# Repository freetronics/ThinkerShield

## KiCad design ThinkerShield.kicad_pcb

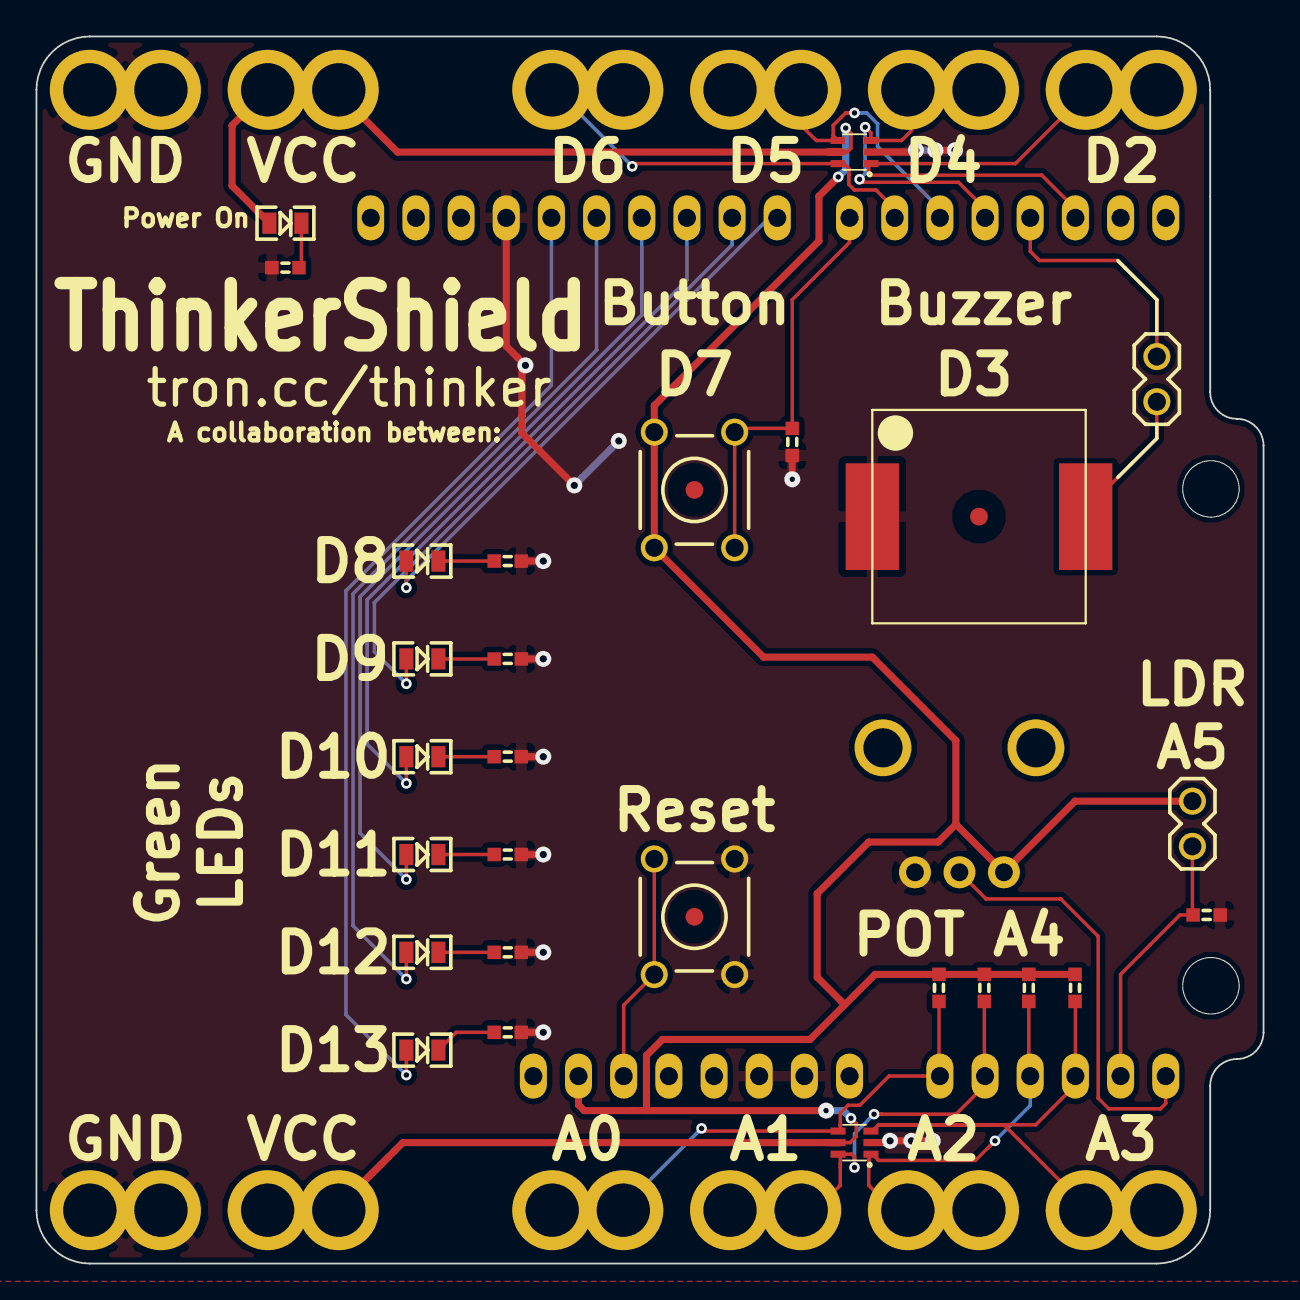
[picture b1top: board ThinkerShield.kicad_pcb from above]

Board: 2 copper layers, 69.0 x 69.0 mm, 46 parts (1 on the bottom side), 29 nets.

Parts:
FIDUCIAL: val**; FIDUCIAL
FIDUCIAL#2, FIDUCIAL#3: val**; FIDUCIAL
JP1, JP2, JP3, JP4, JP5, JP6, JP7, JP8, JP9, JP10, JP11, JP12: M01; ALLIGATOR_CLIP_CONN
JP13: JUMPER2; 1X02
LED1, LED2, LED3, LED4, LED5, LED6: GREEN; LED-0805
LED7: BLUE; LED-0805
LOGO_FREETRONICS: val**; LOGO_FREETRONICS_33mm
LOGO_FREETRONICS#2: val**; LOGO_FREETRONICS_14mm_SolderMask
PH1: LDR GL5516; 1X02
R1: 1K; 0603
R2: 10K; 0603
R3, R4, R10, R11, R12, R13: 470R; 0603
R5, R7, R8, R9: 22M; 0603
R6: 2.2K; 0603
SHIELD1: ARDUINO_SHIELD
SW1, SW2: SW_PUSHBUTTON; SW_PUSHBUTTON_PTH
TV1, TV2: SMF05C; SOT363
U1: BUZZER; BUZZER-12X12-SMT
VR1: 10K; POT_RV09_VERT

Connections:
/A0: JP1.1, R5.1, SHIELD1.AD0, TV1.4
/A1: JP2.1, R7.1, SHIELD1.AD1, TV1.6
/A2: JP3.1, R8.1, SHIELD1.AD2, TV1.1
/A3: JP4.1, R9.1, SHIELD1.AD3, TV1.3
/A4: PH1.2, R1.1, SHIELD1.AD4
/A5: SHIELD1.AD5, VR1.W
/BUZZER: JP13.2, U1.2
/D2: JP9.1, SHIELD1.2, TV2.1
/D3: JP13.1, SHIELD1.3
/D4: JP10.1, SHIELD1.4, TV2.3
/D5: JP11.1, SHIELD1.5, TV2.4
/D6: JP12.1, SHIELD1.6, TV2.6
/D7: R2.1, SHIELD1.7, SW2.2
/D8: LED1.A, SHIELD1.8
/D9: LED2.A, SHIELD1.9
/D10: LED3.A, SHIELD1.10
/D11: LED4.A, SHIELD1.11
/D12: LED5.A, SHIELD1.12
/D13: LED6.A, SHIELD1.13
GND: JP7.1, JP8.1, R1.2, R2.2, R3.1, R4.1, R6.1, R10.1, R11.1, R12.1, R13.1, SHIELD1.GND1, SHIELD1.GND2, SHIELD1.GND3, SW1.2, TV1.2, TV2.2, U1.1, VR1.1
IORef: JP5.1, JP6.1, LED7.A, PH1.1, R5.2, R7.2, R8.2, R9.2, SHIELD1.IO_R, SW2.1, TV1.5, TV2.5, VR1.2
unnamed: LED1.K, R3.2
unnamed: LED2.K, R4.2
unnamed: LED3.K, R10.2
unnamed: LED4.K, R11.2
unnamed: LED5.K, R12.2
unnamed: LED6.K, R13.2
unnamed: LED7.K, R6.2
unnamed: SHIELD1.RST, SW1.1

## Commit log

2015-05-04 First commit, first cut of design
2015-05-04 Remove WS2812B LEDs, add sixth green LED for D13
2015-05-04 Rearrange ESD protection traces, update silkscreen
2015-05-04 Add schematic PDF
2015-05-04 Update gitignore
2015-06-04 Swap TVDS to SMF05C, swap 22M resistors to individual, add body outline around RV09
2015-06-04 Swap pot orientation so CCW = min value
2015-06-04 Add power LED
2015-06-04 Grow alligator clip holes
2015-08-03 Swap A4/A5 to be compatible with older Thinkup boards
2015-08-10 Spread out LEDs, use better MAAS logo
2015-08-27 Split resistor packs into individual resistors, spread LEDs out some more
    Also includes upgrade to KiCad 2015-08 which no longer uses .cmp files
2015-08-27 Resize board designator labels

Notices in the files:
ThinkerShield.kicad_pcb:
Copyright (C) 2015 Freetronics Pty Ltd
TAPR Open Hardware License: tapr.org/ohl
